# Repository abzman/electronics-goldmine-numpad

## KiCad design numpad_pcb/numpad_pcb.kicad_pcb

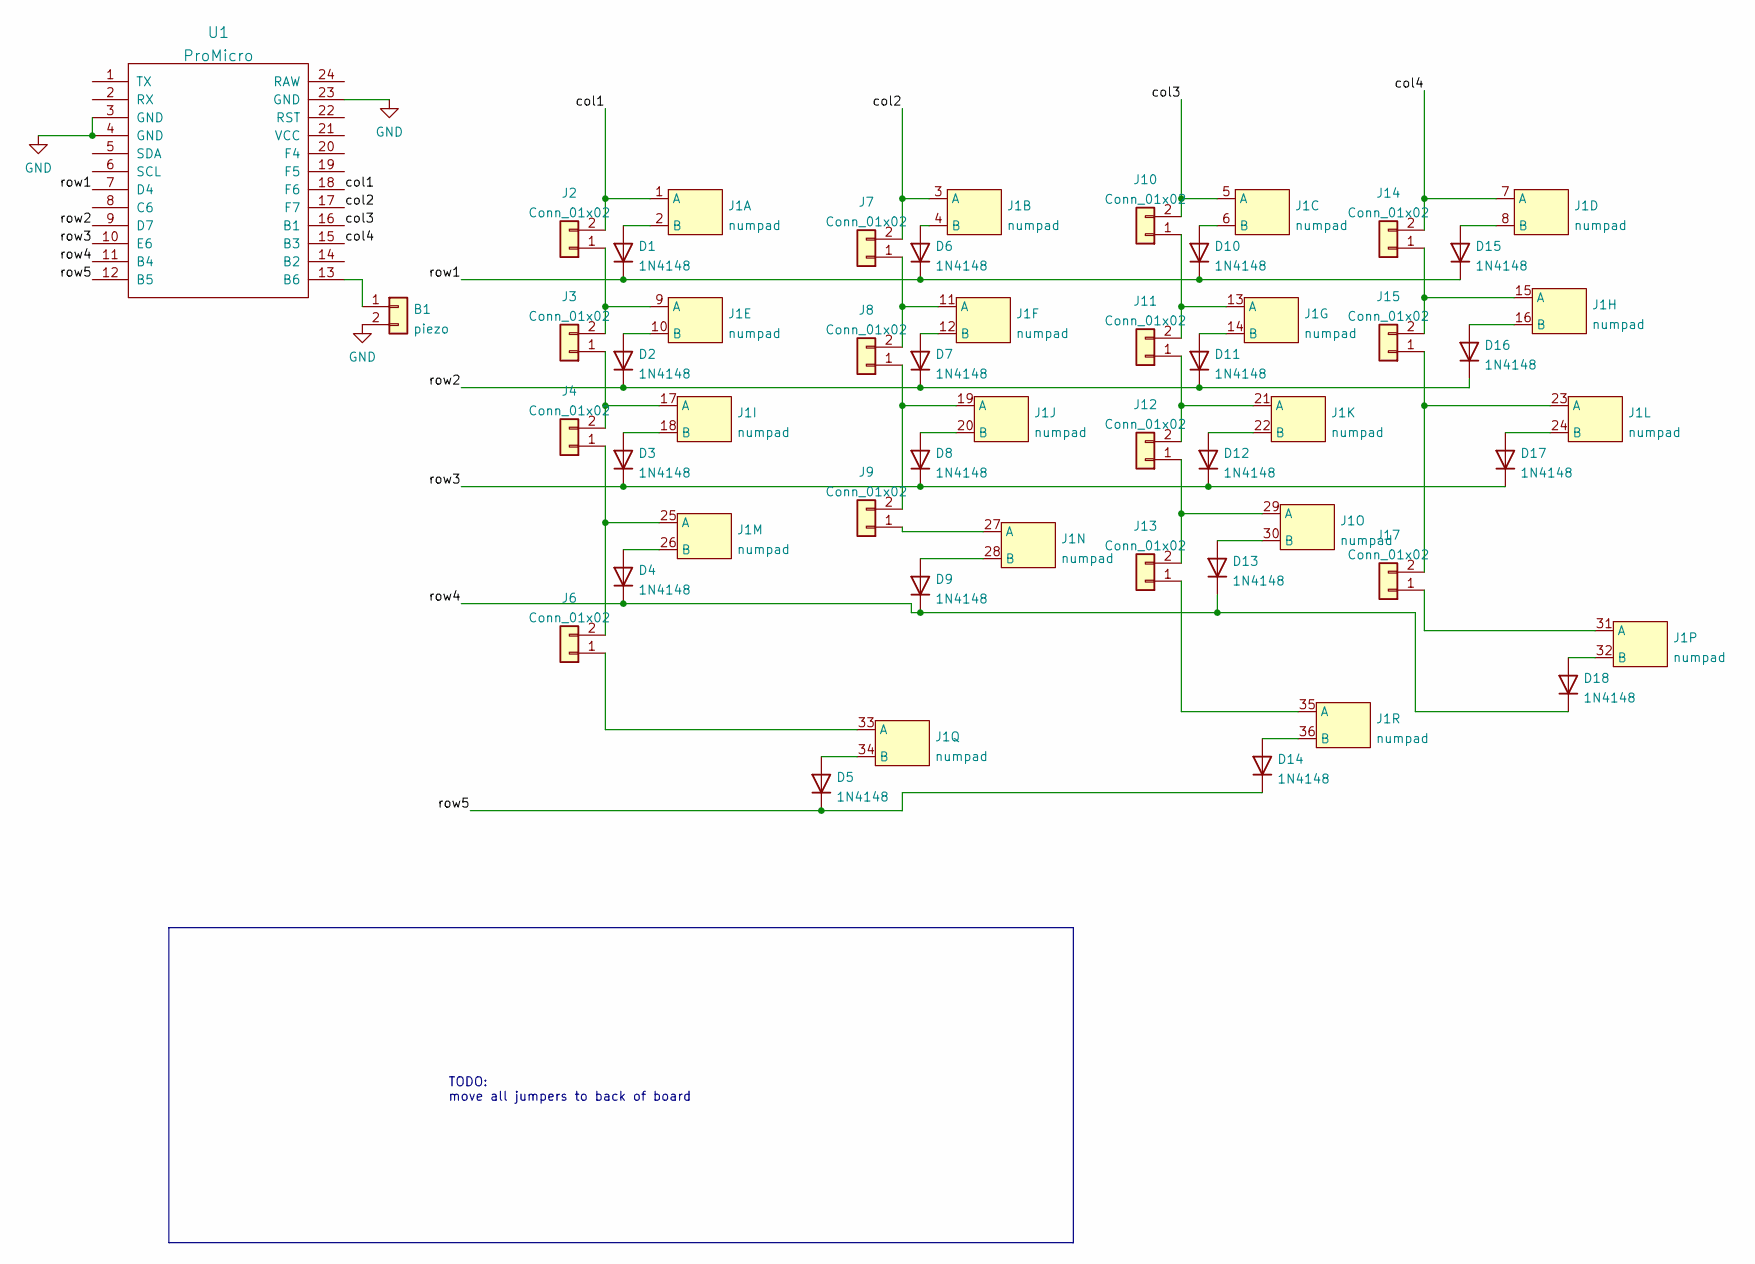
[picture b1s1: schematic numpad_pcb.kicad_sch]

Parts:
B1: piezo; PinHeader_1x02_P2.54mm_Vertical
D1, D2, D3, D4, D5, D6, D7, D8, D9, D10, D11, D12, D13, D14, D15, D16, D17, D18: 1N4148; D_SOD-123F
J1: numpad; electronicsgoldmine_numpad
J2, J3, J4, J6, J7, J8, J9, J10, J11, J12, J13, J14, J15, J17: Conn_01x02; SolderJumper-2_P1.3mm_Open_TrianglePad1.0x1.5mm
U1: ProMicro

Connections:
/col1: J1.1 (A), J2.2, U1.18 (F6)
/col2: J1.3 (A), J7.2, U1.17 (F7)
/col3: J1.5 (A), J10.2, U1.16 (B1)
/col4: J1.7 (A), J14.2, U1.15 (B3)
/row1: D1.1 (K), D6.1 (K), D10.1 (K), D15.1 (K), U1.7 (D4)
/row2: D2.1 (K), D7.1 (K), D11.1 (K), D16.1 (K), U1.9 (D7)
/row3: D3.1 (K), D8.1 (K), D12.1 (K), D17.1 (K), U1.10 (E6)
/row4: D4.1 (K), D9.1 (K), D13.1 (K), D18.1 (K), U1.11 (B4)
/row5: D5.1 (K), D14.1 (K), U1.12 (B5)
GND: B1.2, U1.3 (GND), U1.4 (GND), U1.23 (GND)
unnamed: B1.1, U1.13 (B6)
unnamed: D1.2 (A), J1.2 (B)
unnamed: D2.2 (A), J1.10 (B)
unnamed: D3.2 (A), J1.18 (B)
unnamed: D4.2 (A), J1.26 (B)
unnamed: D5.2 (A), J1.34 (B)
unnamed: D6.2 (A), J1.4 (B)
unnamed: D7.2 (A), J1.12 (B)
unnamed: D8.2 (A), J1.20 (B)
unnamed: D9.2 (A), J1.28 (B)
unnamed: D10.2 (A), J1.6 (B)
unnamed: D11.2 (A), J1.14 (B)
unnamed: D12.2 (A), J1.22 (B)
unnamed: D13.2 (A), J1.30 (B)
unnamed: D14.2 (A), J1.36 (B)
unnamed: D15.2 (A), J1.8 (B)
unnamed: D16.2 (A), J1.16 (B)
unnamed: D17.2 (A), J1.24 (B)
unnamed: D18.2 (A), J1.32 (B)
unnamed: J1.9 (A), J2.1, J3.2
unnamed: J1.11 (A), J7.1, J8.2
unnamed: J1.13 (A), J10.1, J11.2
unnamed: J1.17 (A), J3.1, J4.2
unnamed: J1.19 (A), J8.1, J9.2
unnamed: J1.21 (A), J11.1, J12.2
unnamed: J1.25 (A), J4.1, J6.2
unnamed: J1.27 (A), J9.1
unnamed: J1.29 (A), J12.1, J13.2
unnamed: J1.33 (A), J6.1
unnamed: J1.35 (A), J13.1
unnamed: J1.15 (A), J14.1, J15.2
unnamed: J1.23 (A), J15.1, J17.2
unnamed: J1.31 (A), J17.1

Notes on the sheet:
TODO: move all jumpers to back of board

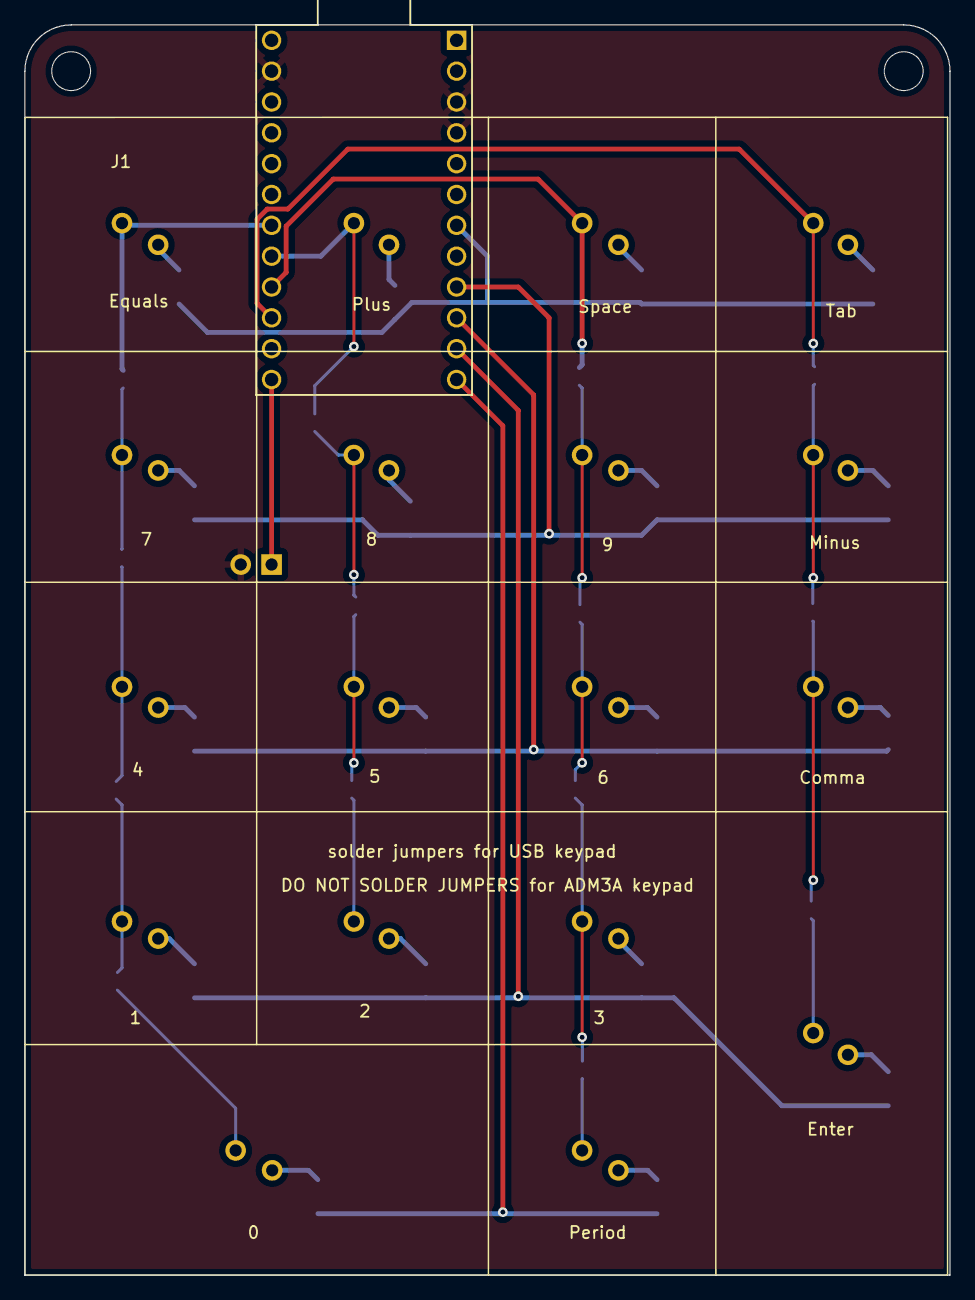
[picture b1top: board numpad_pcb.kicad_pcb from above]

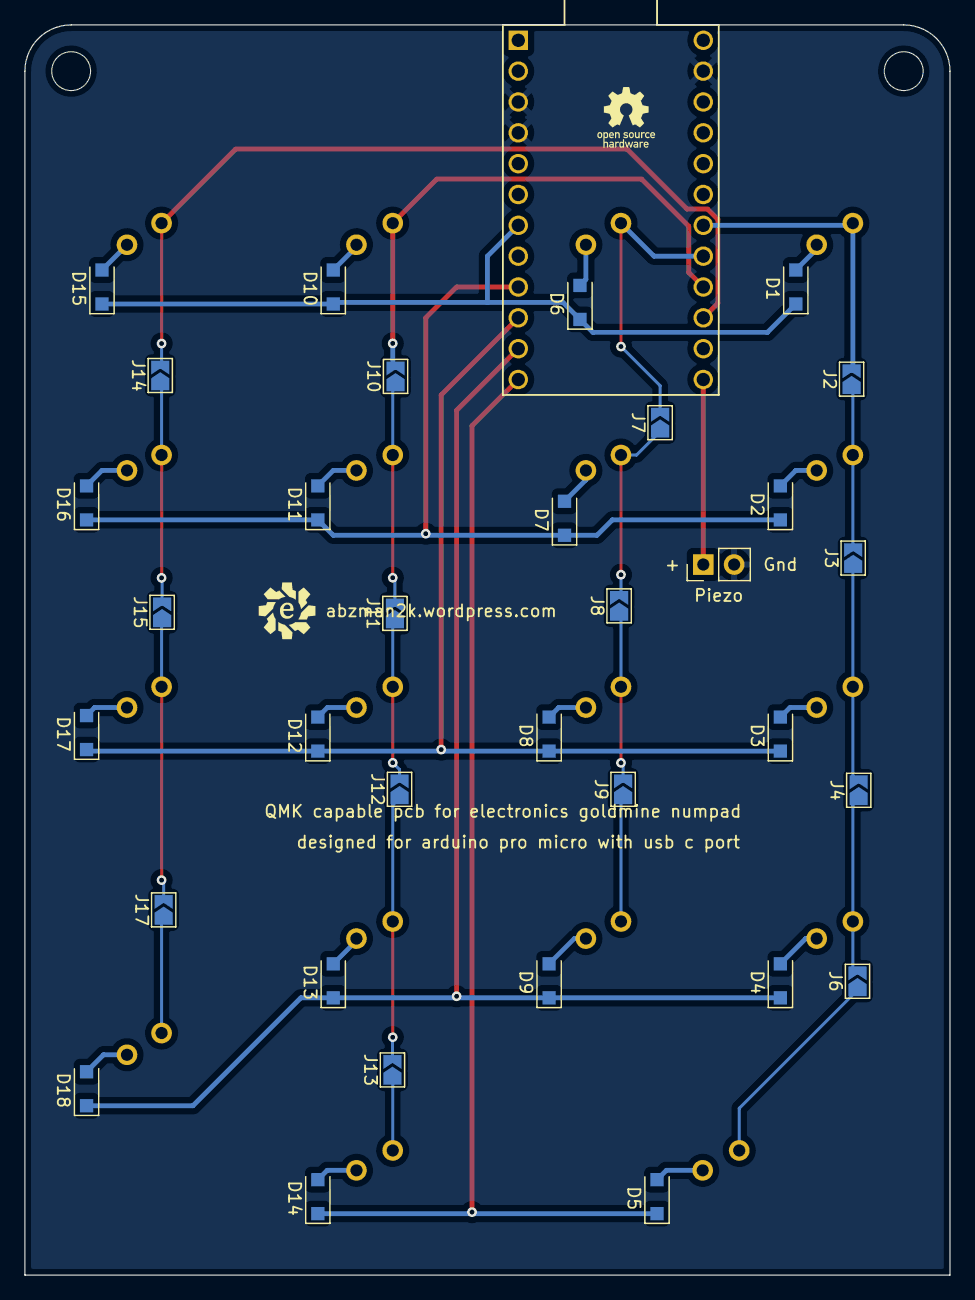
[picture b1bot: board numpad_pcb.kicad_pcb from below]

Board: 2 copper layers, 76.2 x 103.0 mm, 35 parts (34 on the bottom side), 43 nets.

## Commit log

2022-02-15 first layout
2022-02-19 fixed layout to allow for remapping to adm3a pinout
2022-03-13 generated gerbers
2022-03-14 gerber zip
2022-03-29 tweaked silk, added todo for upgraded layout
2022-03-29 tweaked silk, added todo for upgraded layout, added config
2022-04-18 tweaked schematic
2022-05-13 moved jumpers to the back
2022-11-25 added gitignore
2022-12-26 added enclosure
2022-12-30 added qmk json file and some EXEs
2023-12-13 updated project file
